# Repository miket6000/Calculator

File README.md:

# Calculator
This calculator was built to scratch an itch. I wanted a physical RPN calculator similar to the excellent RealCalc. I also wanted an excuse to play around with a pi pico, particuarly their PIO. Finally I wanted a hardware platform to allow me to tinker in firmware and SW as I had ideas and wanted to try something out.

## Status
### Electrical
The PCB is great all circuits have been tested and I'm not aware of any issues. I'm very impressed with the OLED display (photographing it is hard). 

The pico's lowest standby power is only so-so, I can get down to about 980uA which with the 2500mA battery last around 3 months between charges if you only use standby and not the power switch (and significantly less time if the display is left on).

### Mechanical
The 3d printed enclosure and OLED support are perfectly functional, however I wouldn't mind adding more support in the center of the PCB to help dampen some of the button click noise. 

The front panel is a little iffy. The text is too small to easily read, there's not really enough room to make it larger. I also didn't properly consider the mounting so while I did design it with an assembly method in mind, and it does work, there's room for improvement.

### Software
The software is in a good demonstration state. Standby has been implemented to allow low power measurements. The display drivers and basic screen & keyboard abstraction layers have been created as has the skelaton of the ALU. So today you can use it as a basic pocket calculator. This is only a fraction of what I had planned though. 

I wanted to create a macro system so you could record common equations and adjust the variables you want. There's also a softkey function which so far is barely implemented. One softkey is used to put the calculator into standby, the others need defining and a proper system for assigning actions to the soft keys needs to be built.

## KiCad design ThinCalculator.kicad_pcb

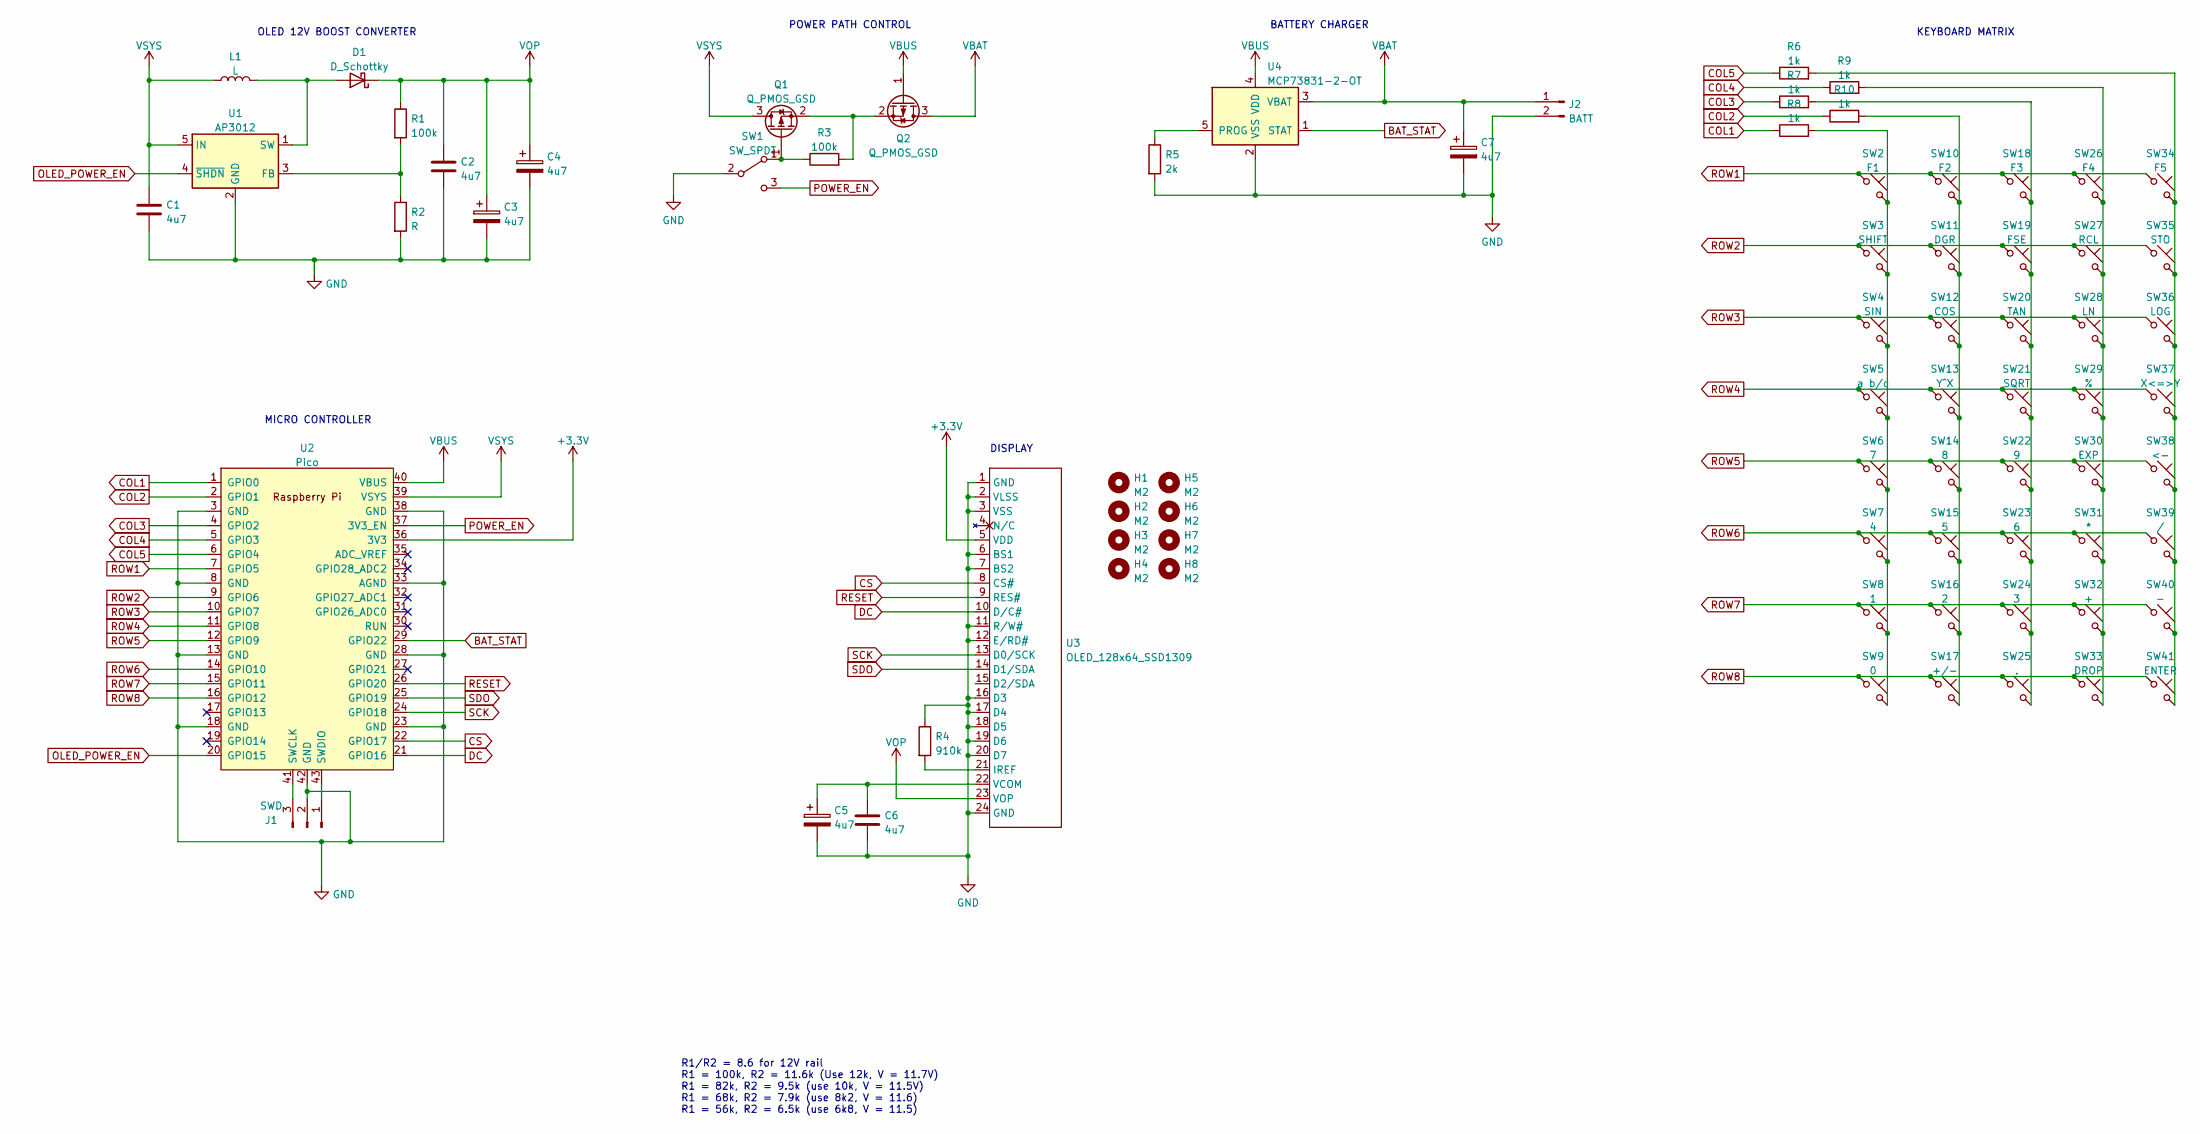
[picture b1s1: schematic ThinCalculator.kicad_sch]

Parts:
C1, C2, C6: 4u7; C_0805_2012Metric_Pad1.18x1.45mm_HandSolder
C3, C4, C5, C7: 4u7; CP_EIA-3216-18_Kemet-A_Pad1.58x1.35mm_HandSolder
D1: D_Schottky; D_SOD-123
H1, H2, H3, H4, H5, H6, H7, H8: M2; MountingHole_2.2mm_M2_ISO7380
J1: SWD; PinHeader_1x03_P2.54mm_Vertical
J2: BATT; JST_EH_S2B-EH_1x02_P2.50mm_Horizontal
L1: L; L_Taiyo-Yuden_NR-30xx_HandSoldering
Q1, Q2: Q_PMOS_GSD; SOT-23
R1, R3: 100k; R_0603_1608Metric_Pad0.98x0.95mm_HandSolder
R2: R; R_0603_1608Metric_Pad0.98x0.95mm_HandSolder
R4: 910k; R_0603_1608Metric_Pad0.98x0.95mm_HandSolder
R5: 2k; R_0603_1608Metric_Pad0.98x0.95mm_HandSolder
R6, R7, R8, R9, R10: 1k; R_0603_1608Metric_Pad0.98x0.95mm_HandSolder
SW1: SW_SPDT; SW_SPDT_CK-JS102011SAQN
SW2: F1; SW_PUSH_6mm
SW3: SHIFT; SW_PUSH_6mm
SW4: SIN; SW_PUSH_6mm
SW5: a b/c; SW_PUSH_6mm
SW6: 7; SW_PUSH_6mm
SW7: 4; SW_PUSH_6mm
SW8: 1; SW_PUSH_6mm
SW9: 0; SW_PUSH_6mm
SW10: F2; SW_PUSH_6mm
SW11: DGR; SW_PUSH_6mm
SW12: COS; SW_PUSH_6mm
SW13: Y^X; SW_PUSH_6mm
SW14: 8; SW_PUSH_6mm
SW15: 5; SW_PUSH_6mm
SW16: 2; SW_PUSH_6mm
SW17: +/-; SW_PUSH_6mm
SW18: F3; SW_PUSH_6mm
SW19: FSE; SW_PUSH_6mm
SW20: TAN; SW_PUSH_6mm
SW21: SQRT; SW_PUSH_6mm
SW22: 9; SW_PUSH_6mm
SW23: 6; SW_PUSH_6mm
SW24: 3; SW_PUSH_6mm
SW25: .; SW_PUSH_6mm
SW26: F4; SW_PUSH_6mm
SW27: RCL; SW_PUSH_6mm
SW28: LN; SW_PUSH_6mm
SW29: %; SW_PUSH_6mm
SW30: EXP; SW_PUSH_6mm
SW31: *; SW_PUSH_6mm
SW32: +; SW_PUSH_6mm
SW33: DROP; SW_PUSH_6mm
SW34: F5; SW_PUSH_6mm
SW35: STO; SW_PUSH_6mm
SW36: LOG; SW_PUSH_6mm
SW37: X<=>Y; SW_PUSH_6mm
SW38: <-; SW_PUSH_6mm
SW39: /; SW_PUSH_6mm
SW40: -; SW_PUSH_6mm
SW41: ENTER; SW_PUSH_6mm
U1: AP3012; SOT-23-5
U2: Pico; RPi_Pico_SMD_TH__Reverse_Mount
U3: OLED_128x64_SSD1309; Hirose_FH12-24S-0.5SH_1x24-1MP_P0.50mm_Horizontal
U4: MCP73831-2-OT; SOT-23-5

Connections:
+3V3: U2.36 (3V3), U3.5 (VDD)
BAT_STAT: U2.29 (GPIO22), U4.1 (STAT)
COL1: R8.1, U2.1 (GPIO0)
COL2: R10.1, U2.2 (GPIO1)
COL3: R7.1, U2.4 (GPIO2)
COL4: R9.1, U2.5 (GPIO3)
COL5: R6.1, U2.6 (GPIO4)
CS: U2.22 (GPIO17), U3.8 (CS#)
DC: U2.21 (GPIO16), U3.10 (D/C#)
GND: C1.2, C2.2, C3.2, C4.2, C5.2, C6.2, C7.2, J1.2, J2.2, R2.2, R4.1, R5.2, SW1.2 (B), U1.2 (GND), U2.3 (GND), U2.8 (GND), U2.13 (GND), U2.18 (GND), U2.23 (GND), U2.28 (GND), U2.33 (AGND), U2.38 (GND), U2.42 (GND), U3.1 (GND), U3.2 (VLSS), U3.3 (VSS), U3.6 (BS1), U3.7 (BS2), U3.11 (R/W#), U3.12 (E/RD#), U3.16 (D3), U3.17 (D4), U3.18 (D5), U3.19 (D6), U3.20 (D7), U3.24 (GND), U4.2 (VSS)
unnamed: C5.1, C6.1, U3.22 (VCOM)
unnamed: D1.2 (A), L1.2, U1.1 (SW)
unnamed: J1.1, U2.43 (SWDIO)
unnamed: J1.3, U2.41 (SWCLK)
unnamed: Q1.1 (G), R3.1, SW1.1 (A)
unnamed: Q1.2 (S), Q2.2 (S), R3.2
unnamed: R1.2, R2.1, U1.3 (FB)
unnamed: R4.2, U3.21 (IREF)
unnamed: R5.1, U4.5 (PROG)
unnamed: R6.2, SW34.2, SW35.2, SW36.2, SW37.2, SW38.2, SW39.2, SW40.2, SW41.2
unnamed: R7.2, SW18.2, SW19.2, SW20.2, SW21.2, SW22.2, SW23.2, SW24.2, SW25.2
unnamed: R8.2, SW2.2, SW3.2, SW4.2, SW5.2, SW6.2, SW7.2, SW8.2, SW9.2
unnamed: R9.2, SW26.2, SW27.2, SW28.2, SW29.2, SW30.2, SW31.2, SW32.2, SW33.2
unnamed: R10.2, SW10.2, SW11.2, SW12.2, SW13.2, SW14.2, SW15.2, SW16.2, SW17.2
OLED_POWER_EN: U1.4 (~SHDN), U2.20 (GPIO15)
POWER_EN: SW1.3 (C), U2.37 (3V3_EN)
RESET: U2.26 (GPIO20), U3.9 (RES#)
ROW1: SW2.1, SW10.1, SW18.1, SW26.1, SW34.1, U2.7 (GPIO5)
ROW2: SW3.1, SW11.1, SW19.1, SW27.1, SW35.1, U2.9 (GPIO6)
ROW3: SW4.1, SW12.1, SW20.1, SW28.1, SW36.1, U2.10 (GPIO7)
ROW4: SW5.1, SW13.1, SW21.1, SW29.1, SW37.1, U2.11 (GPIO8)
ROW5: SW6.1, SW14.1, SW22.1, SW30.1, SW38.1, U2.12 (GPIO9)
ROW6: SW7.1, SW15.1, SW23.1, SW31.1, SW39.1, U2.14 (GPIO10)
ROW7: SW8.1, SW16.1, SW24.1, SW32.1, SW40.1, U2.15 (GPIO11)
ROW8: SW9.1, SW17.1, SW25.1, SW33.1, SW41.1, U2.16 (GPIO12)
SCK: U2.24 (GPIO18), U3.13 (D0/SCK)
SDO: U2.25 (GPIO19), U3.14 (D1/SDA)
VBAT: C7.1, J2.1, Q2.3 (D), U4.3 (VBAT)
VBUS: Q2.1 (G), U2.40 (VBUS), U4.4 (VDD)
VOP: C2.1, C3.1, C4.1, D1.1 (K), R1.1, U3.23 (VOP)
VSYS: C1.1, L1.1, Q1.3 (D), U1.5 (IN), U2.39 (VSYS)

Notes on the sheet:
MICRO CONTROLLER
POWER PATH CONTROL
OLED 12V BOOST CONVERTER
DISPLAY
BATTERY CHARGER
R1/R2 = 8.6 for 12V rail R1 = 100k, R2 = 11.6k (Use 12k, V = 11.7V) R1 = 82k, R2 = 9.5k (use 10k, V = 11.5V) R1 = 68k, R2 = 7.9k (use 8k2, V = 11.6) R1 = 56k, R2 = 6.5k (use 6k8, V = 11.5)
KEYBOARD MATRIX

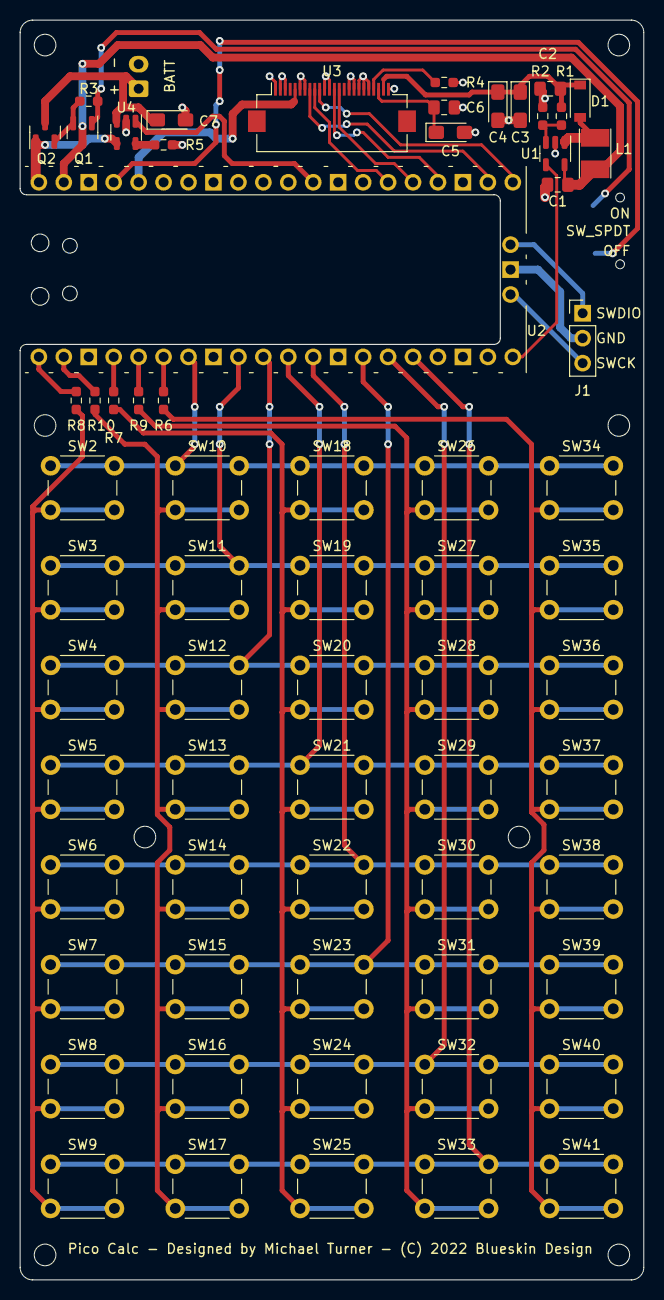
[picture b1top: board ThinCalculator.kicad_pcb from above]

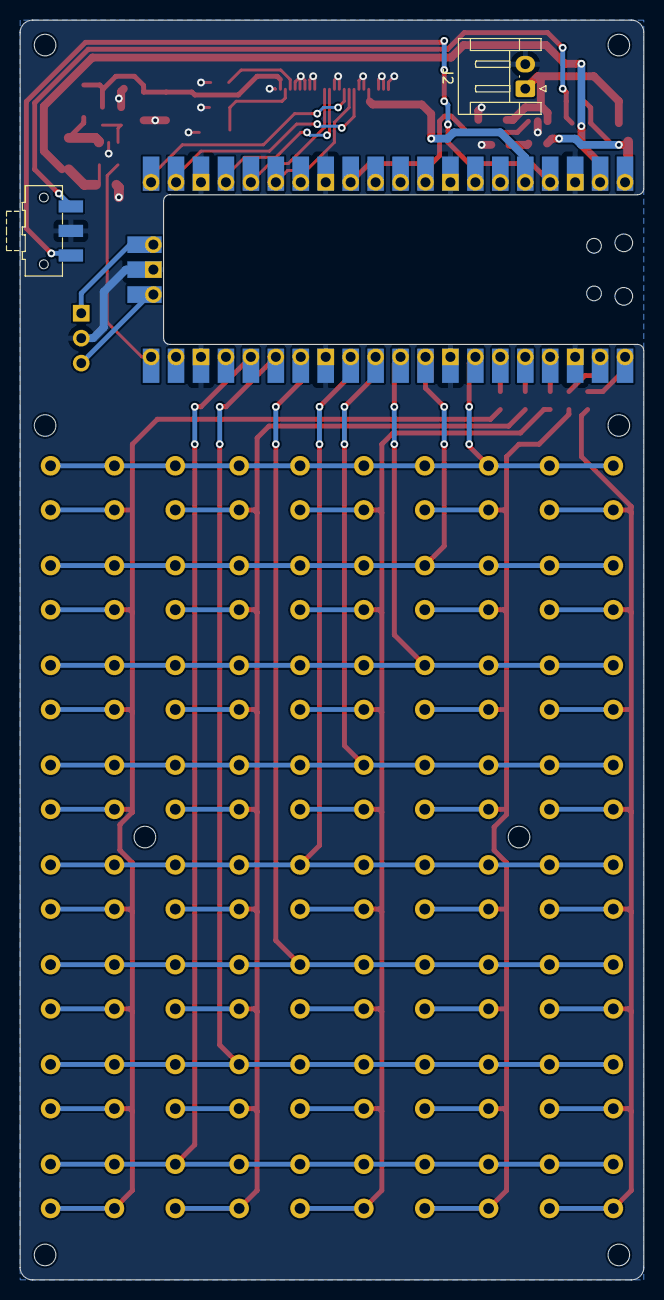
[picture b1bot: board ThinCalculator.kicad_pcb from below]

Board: 2 copper layers, 63.5 x 128.2 mm, 76 parts (2 on the bottom side), 41 nets.

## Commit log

2022-12-14 production version 1.0

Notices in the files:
ThinCalculator.kicad_pcb:
Pico Calc - Designed by Michael Turner - (C) 2022 Blueskin Design
